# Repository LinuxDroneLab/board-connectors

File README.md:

# board-connectors
simple electronic board for the frame tarot 650, the GY-521 and Beagle Bone Black

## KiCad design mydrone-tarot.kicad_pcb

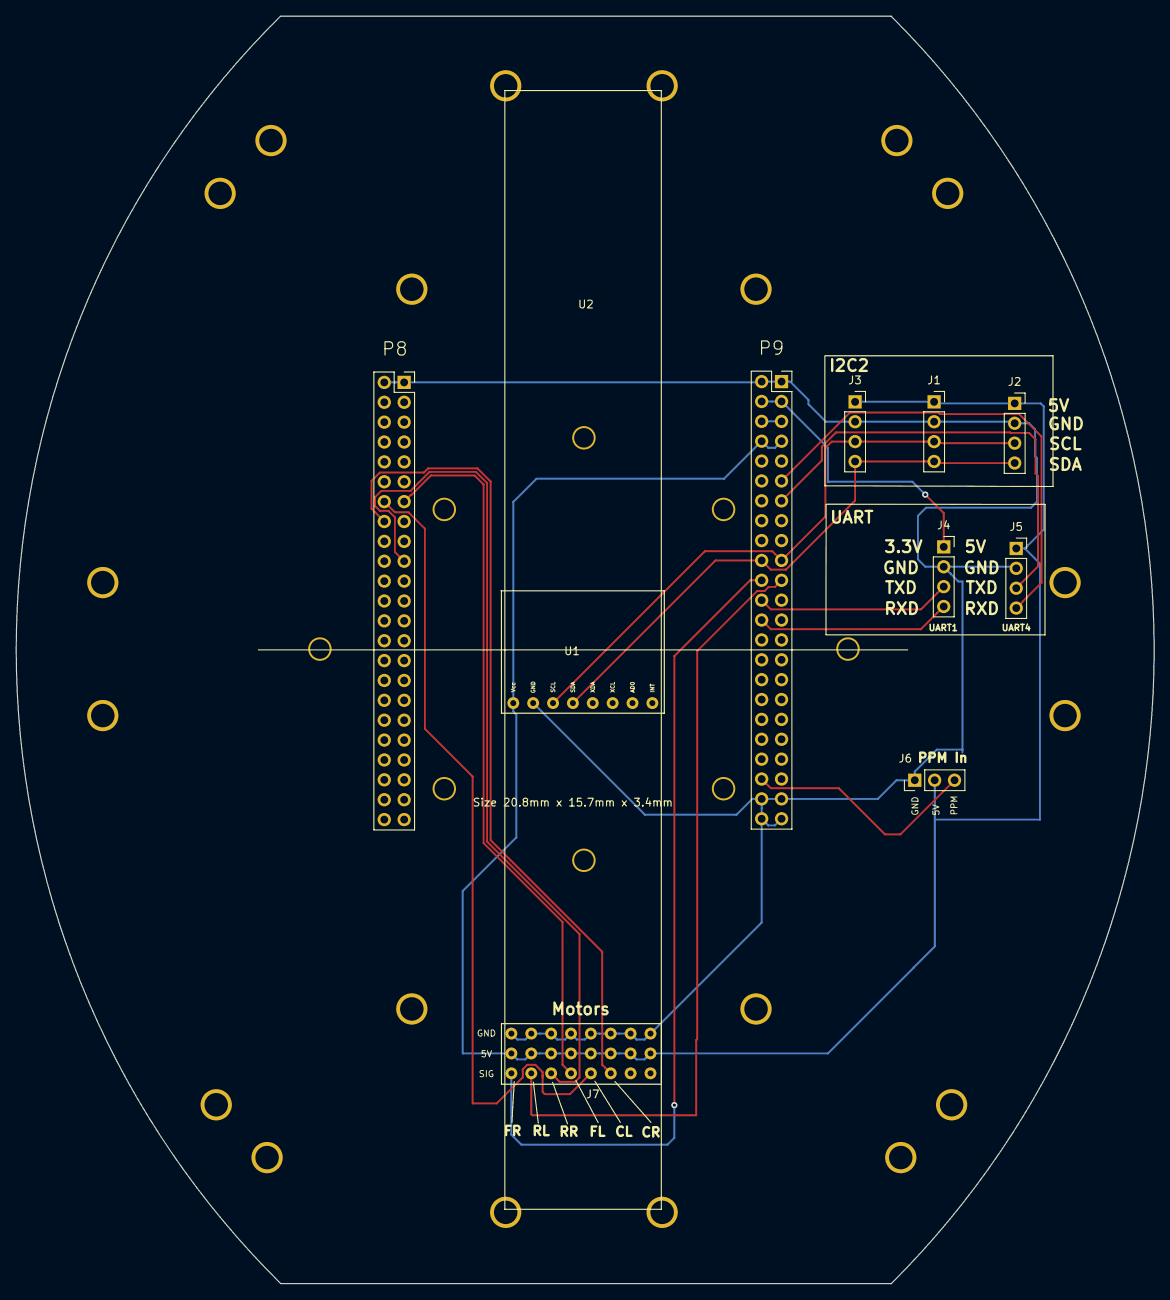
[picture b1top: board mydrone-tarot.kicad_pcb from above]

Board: 2 copper layers, 145.5 x 162.0 mm, 11 parts (0 on the bottom side), 17 nets.

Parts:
J1, J2, J3, J4, J5: Conn_01x04; PinSocket_1x04_P2.54mm_Vertical
J6: Conn_01x03; PinHeader_1x03_P2.54mm_Vertical
J7: Conn_01x24; Conn_PinHeader_3x8_2_54mm_footprint
P8, P9: Conn_02x23_Odd_Even; PinSocket_2x23_P2.54mm_Vertical
U1: GY-521; gy-521_footprint
U2: tarot_scheda_superiore; tarot_650

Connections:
/DGND: J1.2, J2.2, J3.2, J4.2, J5.2, J6.1, J7.1, J7.4, J7.7, J7.10, J7.13, J7.16, J7.19, J7.22, P8.1, P8.2, P9.1, P9.2, P9.43, P9.44, P9.45, P9.46, U1.2
/I2C2_SCL: J1.3, J2.3, J3.3, P9.19, U1.3
/I2C2_SDA: J1.4, J2.4, J3.4, P9.20, U1.4
/PPM: J6.3, P9.42
/PWM0_A: J7.3, P9.22
/PWM0_B: J7.6, P9.21
/PWM1_A: J7.15, P8.14
/PWM1_B: J7.18, P8.16
/PWM2_A: J7.9, P8.19
/PWM2_B: J7.12, P8.13
/SYS_5V: J1.1, J2.1, J3.1, J5.1, J6.2, J7.2, J7.5, J7.8, J7.11, J7.14, J7.17, J7.20, J7.23, P9.7, P9.8, U1.1
/UART1_RXD: J4.4, P9.26
/UART1_TXD: J4.3, P9.24
/UART4_RXD: J5.4, P9.11
/UART4_TXD: J5.3, P9.13
/VDD_3V3: J4.1, P9.3, P9.4
/VDD_5V: P9.5, P9.6

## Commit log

2018-11-15 Primo commit
